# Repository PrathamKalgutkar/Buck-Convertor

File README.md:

Buck Convertor designed for IIT Madras's EE4102 - "Electronic Product Design" Course Project
Contained in the Repository are the KiCAD project Files, CSV file for Bill of Materials and PDF File of Final Report submitted to Course Instructor

The Project consisted of :
- Design of Buck Convertor
- Derivation of Component Values
- Design of Circuit Schematic
- Design of DRC checked PCB Board
- 3D View of the Designed PCB
- Estimation of Convertor Efficiency
- Bill of Materials

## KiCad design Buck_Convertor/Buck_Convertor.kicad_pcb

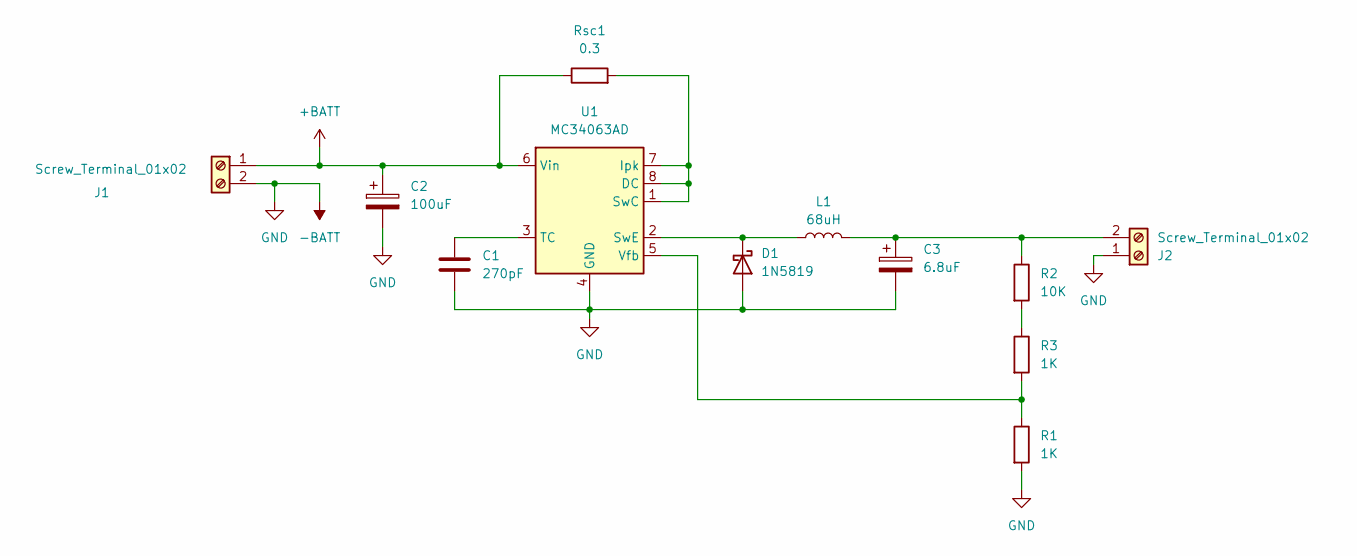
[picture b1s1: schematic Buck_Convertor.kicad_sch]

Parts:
C1: 270pF; C_0805_2012Metric_Pad1.18x1.45mm_HandSolder
C2: 100uF; CP_Radial_D6.3mm_P2.50mm
C3: 6.8uF; CP_Radial_D8.0mm_P3.50mm
D1: 1N5819; D_DO-41_SOD81_P10.16mm_Horizontal
J1, J2: Screw_Terminal_01x02; TerminalBlock_Phoenix_MKDS-1,5-2_1x02_P5.00mm_Horizontal
L1: 68uH; L_Sunlord_MWSA0624S
R1, R3: 1K; R_Axial_DIN0207_L6.3mm_D2.5mm_P10.16mm_Horizontal
R2: 10K; R_Axial_DIN0207_L6.3mm_D2.5mm_P10.16mm_Horizontal
Rsc1: 0.3; R_1210_3225Metric
U1: MC34063AD; SOIC-8_3.9x4.9mm_P1.27mm

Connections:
+BATT: C2.1, J1.1, Rsc1.1, U1.6 (Vin)
-BATT: C1.2, C2.2, C3.2, D1.2 (A), J1.2, J2.1, R1.2, U1.4 (GND)
unnamed: D1.1 (K), L1.1, U1.2 (SwE)
unnamed: C3.1, J2.2, L1.2, R2.1
unnamed: R2.2, R3.1
unnamed: Rsc1.2, U1.1 (SwC), U1.7 (Ipk), U1.8 (DC)
unnamed: C1.1, U1.3 (TC)
unnamed: R1.1, R3.2, U1.5 (Vfb)

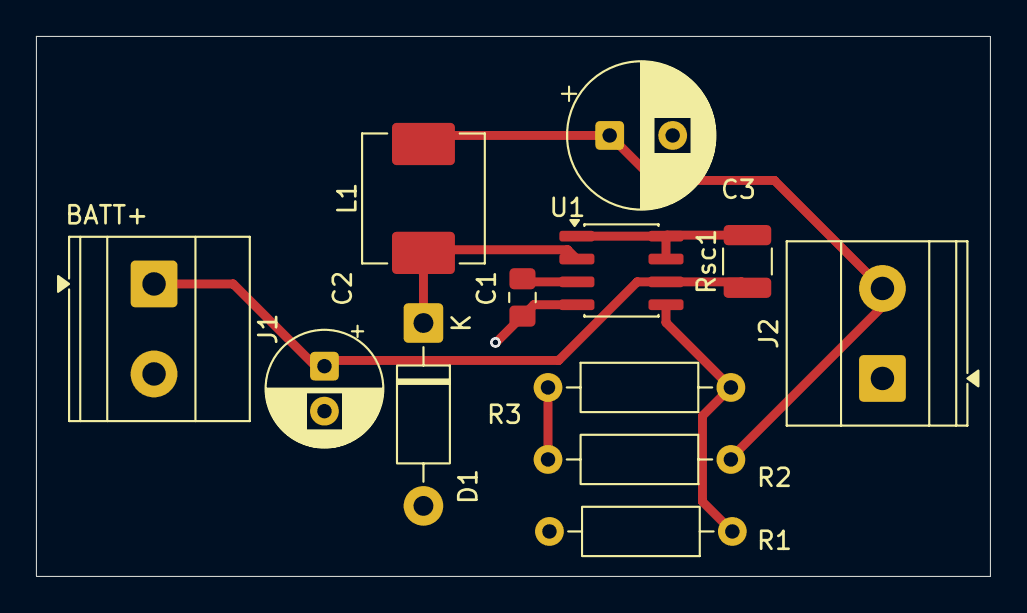
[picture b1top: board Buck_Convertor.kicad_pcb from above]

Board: 2 copper layers, 53.0 x 30.0 mm, 12 parts (0 on the bottom side), 8 nets.

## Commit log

2025-12-24 KiCAD Files
    Project, Scheamtic and Board Files for the KiCAD Project
2025-12-24 BOM File
2025-12-24 Final Report
2025-12-24 Create README.md
    Basic Description of the project
